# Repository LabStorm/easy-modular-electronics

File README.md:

# easy-modular-electronics
A library of tiny interconnectable modules to create electronics systems. A module consists of a small electronic circuit with a single-purpose (for example, a voltage stabilizer, an instrumentation amplifier or a PIR sensor. 

## Modules
The 'modules/template' folder contains (TO DO) a template which can be used as a starting point to create new modules. 

## Mechanical/Electrical Specs

TO DO

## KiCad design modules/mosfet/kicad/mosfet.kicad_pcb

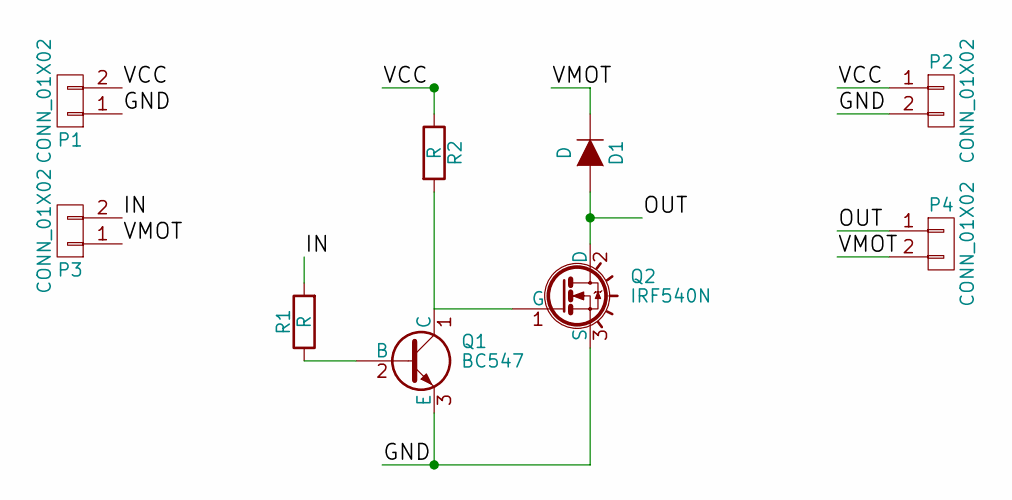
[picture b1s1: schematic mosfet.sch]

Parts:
D1: D; Diode_DO-35_SOD27_Horizontal_RM10
P1, P2, P3, P4: CONN_01X02; Pin_Header_Angled_1x02
Q1: BC547; TO-92_Molded_Narrow
Q2: IRF540N; TO-220_Neutral123_Vertical_LargePads
R1, R2: R; Resistor_Horizontal_RM7mm

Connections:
/GND: P1.1, P2.2, Q1.3 (E), Q2.3 (S)
/IN: P3.2, R1.2
/OUT: D1.2 (A), P4.1, Q2.2 (D)
/VCC: P1.2, P2.1, R2.1
/VMOT: D1.1 (K), P3.1, P4.2
unnamed: Q1.1 (C), Q2.1 (G), R2.2
unnamed: Q1.2 (B), R1.1

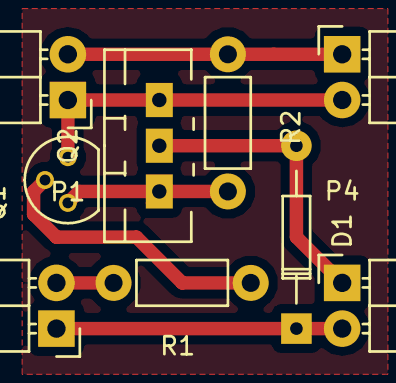
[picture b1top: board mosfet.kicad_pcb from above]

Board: 2 copper layers, 9 parts (0 on the bottom side), 7 nets.

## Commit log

2016-11-10 Added module: mosfet
2016-11-11 Mosfet Box Freecad Files
    First Commit!!
2016-11-23 Fixes issue #1
